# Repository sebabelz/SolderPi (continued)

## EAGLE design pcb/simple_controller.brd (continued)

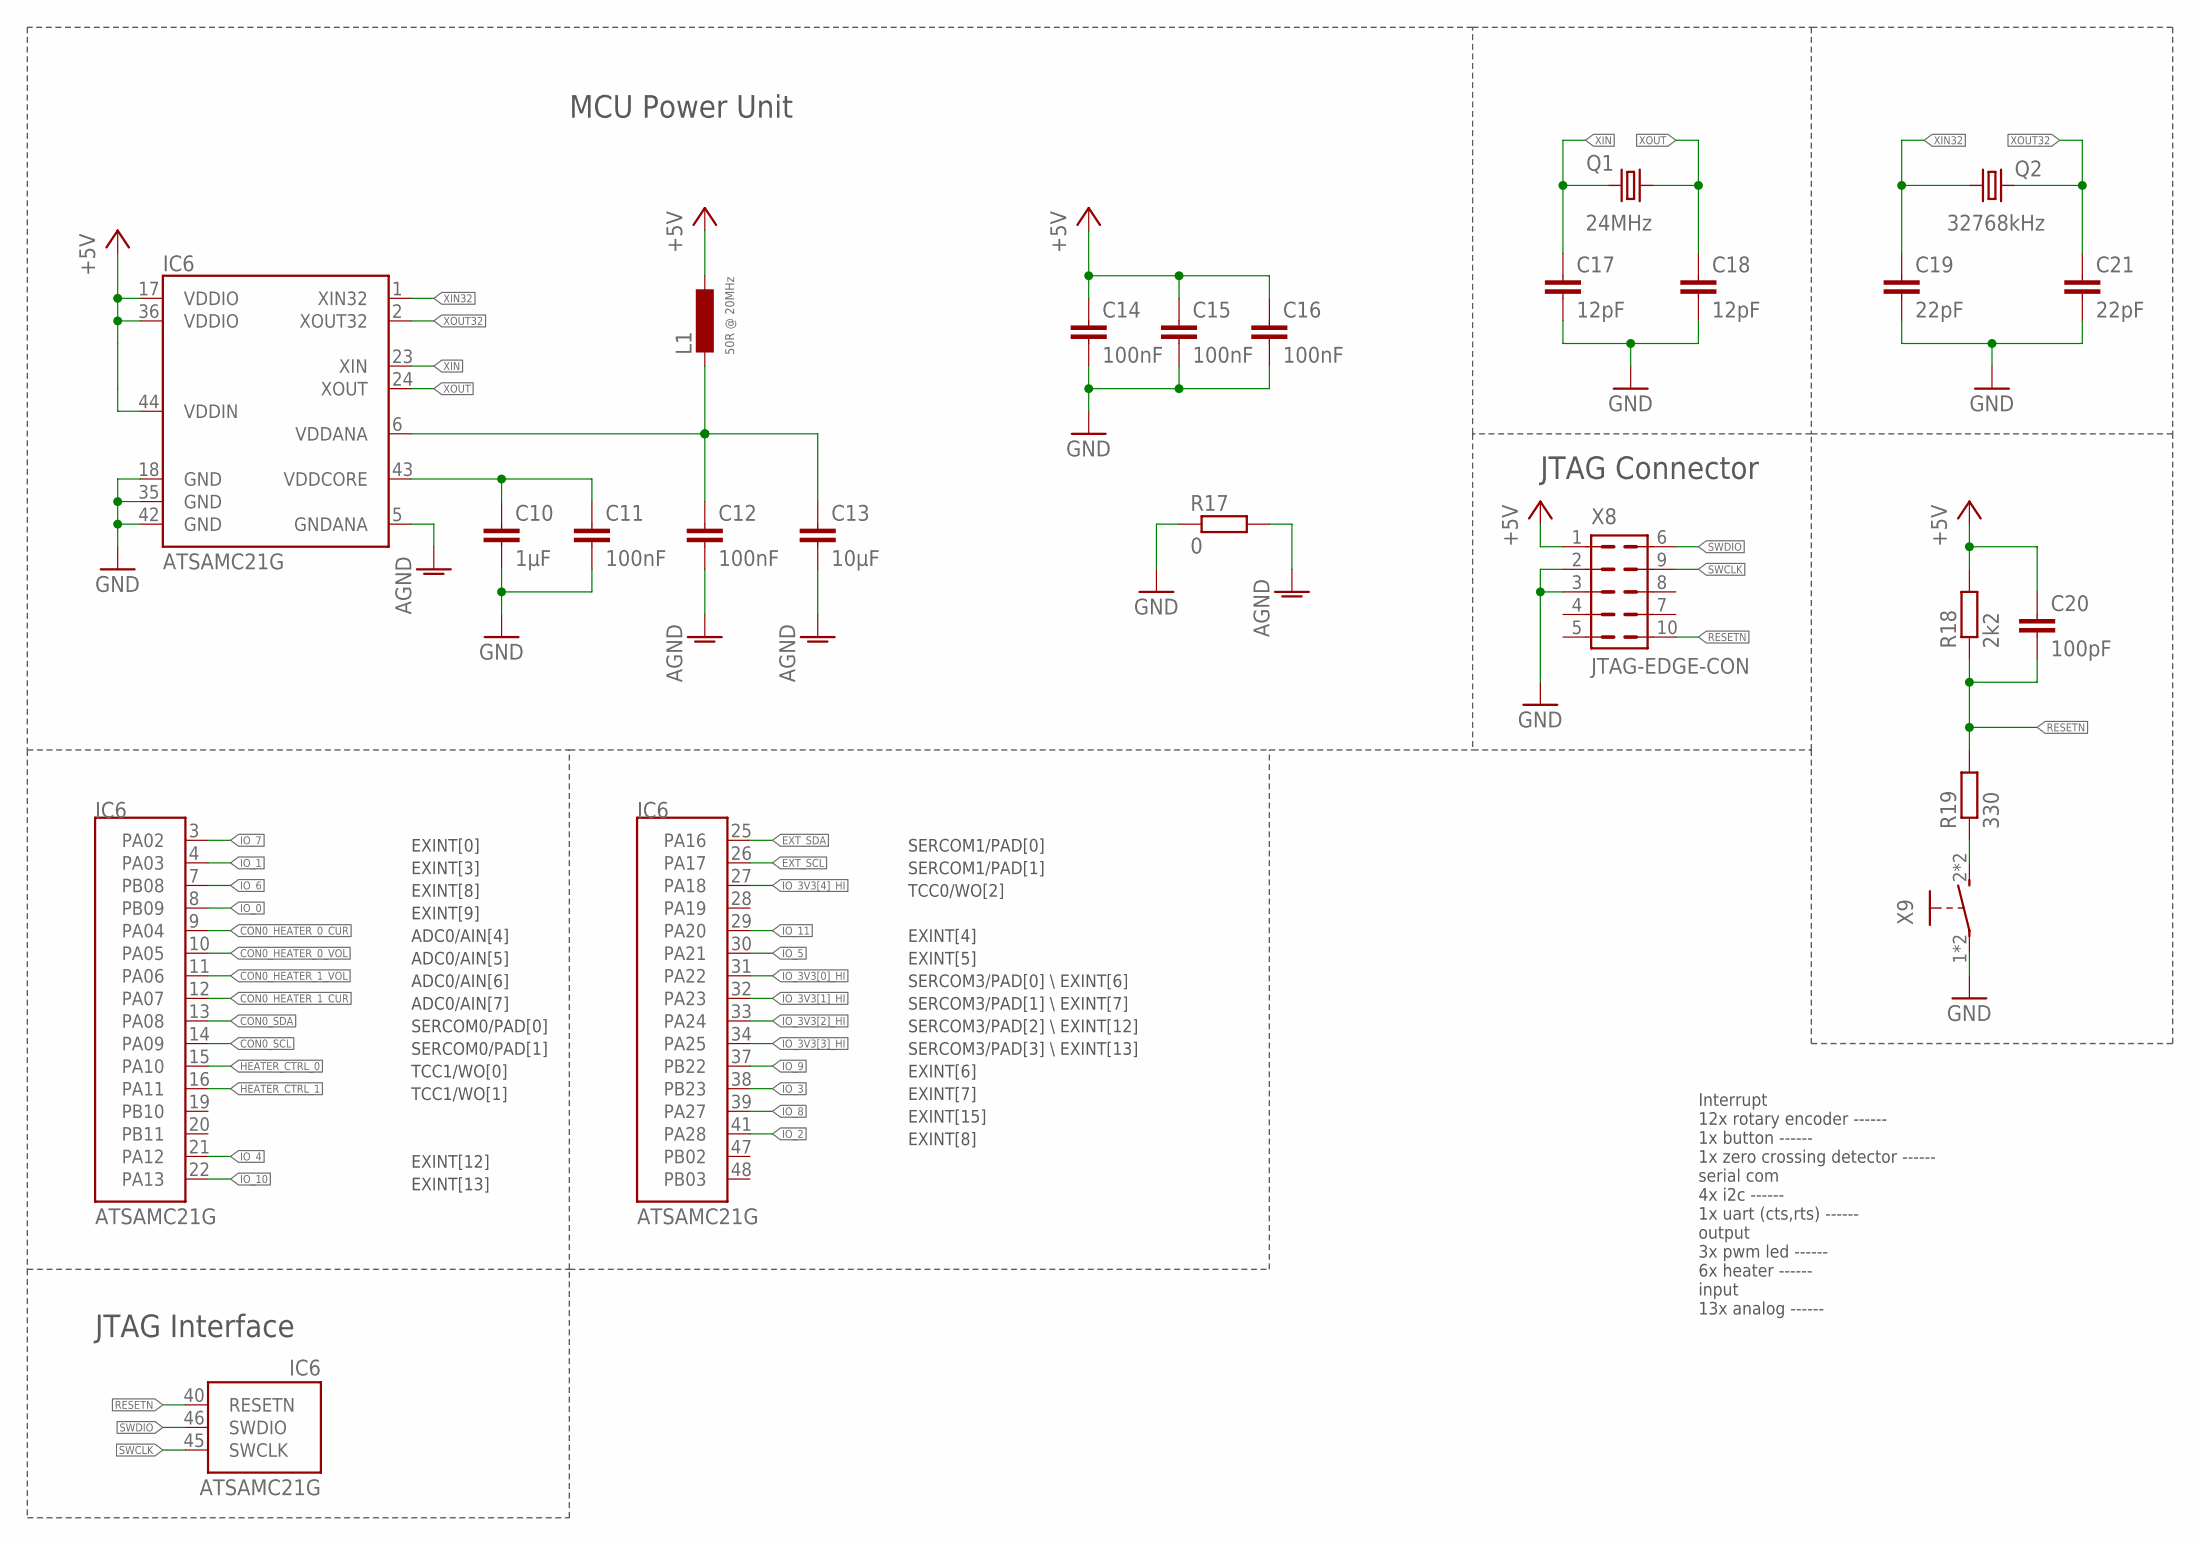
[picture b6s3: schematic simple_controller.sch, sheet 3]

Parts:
C10: 1µF; C0402
C11, C12, C14, C15, C16: 100nF; C0402
C13: 10µF; C0805
C17, C18: 12pF; C0402
C19, C21: 22pF; C0402
C20: 100pF; C0603
IC6: ATSAMC21G; TQFP48
L1: 50R @ 20MHz; L0603
Q1: 24MHz; HCR2520
Q2: 32768kHz; 2X1.2
R17: 0; R1210
R18: 2k2; R0603
R19: 330; R0603
X8: JTAG-EDGE-CON; DEBUG-CON
X9: B3S-1000; B3S

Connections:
+5V: C14.1, C15.1, C16.1, C20.1, IC6.17 (VDDIO), IC6.36 (VDDIO), IC6.44 (VDDIN), L1.1, R18.2, X8.1; also elsewhere on the board
AGND: C12.2, C13.2, IC6.5 (GNDANA), R17.2; also elsewhere on the board
CON0_HEATER_0_CUR: IC6.9 (PA04); also elsewhere on the board
CON0_HEATER_0_VOL: IC6.10 (PA05); also elsewhere on the board
CON0_HEATER_1_CUR: IC6.12 (PA07); also elsewhere on the board
CON0_HEATER_1_VOL: IC6.11 (PA06); also elsewhere on the board
CON0_SCL: IC6.14 (PA09); also elsewhere on the board
CON0_SDA: IC6.13 (PA08); also elsewhere on the board
EXT_SCL: IC6.26 (PA17); also elsewhere on the board
EXT_SDA: IC6.25 (PA16); also elsewhere on the board
GND: C10.2, C11.2, C14.2, C15.2, C16.2, C17.2, C18.2, C19.2, C21.2, IC6.18 (GND), IC6.35 (GND), IC6.42 (GND), R17.1, X8.2, X8.3, X9.1, X9.3; also elsewhere on the board
HEATER_CTRL_0: IC6.15 (PA10); also elsewhere on the board
HEATER_CTRL_1: IC6.16 (PA11); also elsewhere on the board
IO_0: IC6.8 (PB09); also elsewhere on the board
IO_1: IC6.4 (PA03); also elsewhere on the board
IO_2: IC6.41 (PA28); also elsewhere on the board
IO_3: IC6.38 (PB23); also elsewhere on the board
IO_3V3[0]_HI: IC6.31 (PA22); also elsewhere on the board
IO_3V3[1]_HI: IC6.32 (PA23); also elsewhere on the board
IO_3V3[2]_HI: IC6.33 (PA24); also elsewhere on the board
IO_3V3[3]_HI: IC6.34 (PA25); also elsewhere on the board
IO_3V3[4]_HI: IC6.27 (PA18); also elsewhere on the board
IO_4: IC6.21 (PA12); also elsewhere on the board
IO_5: IC6.30 (PA21); also elsewhere on the board
IO_6: IC6.7 (PB08); also elsewhere on the board
IO_7: IC6.3 (PA02); also elsewhere on the board
IO_8: IC6.39 (PA27); also elsewhere on the board
IO_9: IC6.37 (PB22); also elsewhere on the board
IO_10: IC6.22 (PA13); also elsewhere on the board
IO_11: IC6.29 (PA20); also elsewhere on the board
RESETN: C20.2, IC6.40 (RESETN), R18.1, R19.2, X8.10; also elsewhere on the board
RESET_SW_IN: R19.1, X9.2 (S), X9.4 (S)
SWCLK: IC6.45 (SWCLK), X8.9; also elsewhere on the board
SWDIO: IC6.46 (SWDIO), X8.6; also elsewhere on the board
VDDANA: C12.1, C13.1, IC6.6 (VDDANA), L1.2
VDDCORE: C10.1, C11.1, IC6.43 (VDDCORE)
XIN: C17.1, IC6.23 (XIN), Q1.1
XIN32: C19.1, IC6.1 (XIN32), Q2.1
XOUT: C18.1, IC6.24 (XOUT), Q1.2
XOUT32: C21.1, IC6.2 (XOUT32), Q2.2

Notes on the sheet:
Interrupt 12x rotary encoder ------ 1x button ------ 1x zero crossing detector ------ serial com 4x i2c ------ 1x uart (cts,rts) ------ output 3x pwm led ------ 6x heater ------ input 13x analog ------
JTAG Interface
JTAG Connector
MCU Power Unit
TCC1/WO[1]
TCC1/WO[0]
ADC0/AIN[4]
ADC0/AIN[5]
ADC0/AIN[6]
ADC0/AIN[7]
SERCOM0/PAD[0]
SERCOM0/PAD[1]
SERCOM1/PAD[0]
SERCOM1/PAD[1]
SERCOM3/PAD[0] \\ EXINT[6]
SERCOM3/PAD[1] \\ EXINT[7]
SERCOM3/PAD[2] \\ EXINT[12]
SERCOM3/PAD[3] \\ EXINT[13]
TCC0/WO[2]
EXINT[9]
EXINT[8]
EXINT[3]
EXINT[0]
EXINT[15]
EXINT[7]
EXINT[6]
EXINT[13]
EXINT[12]
EXINT[4]
EXINT[5]

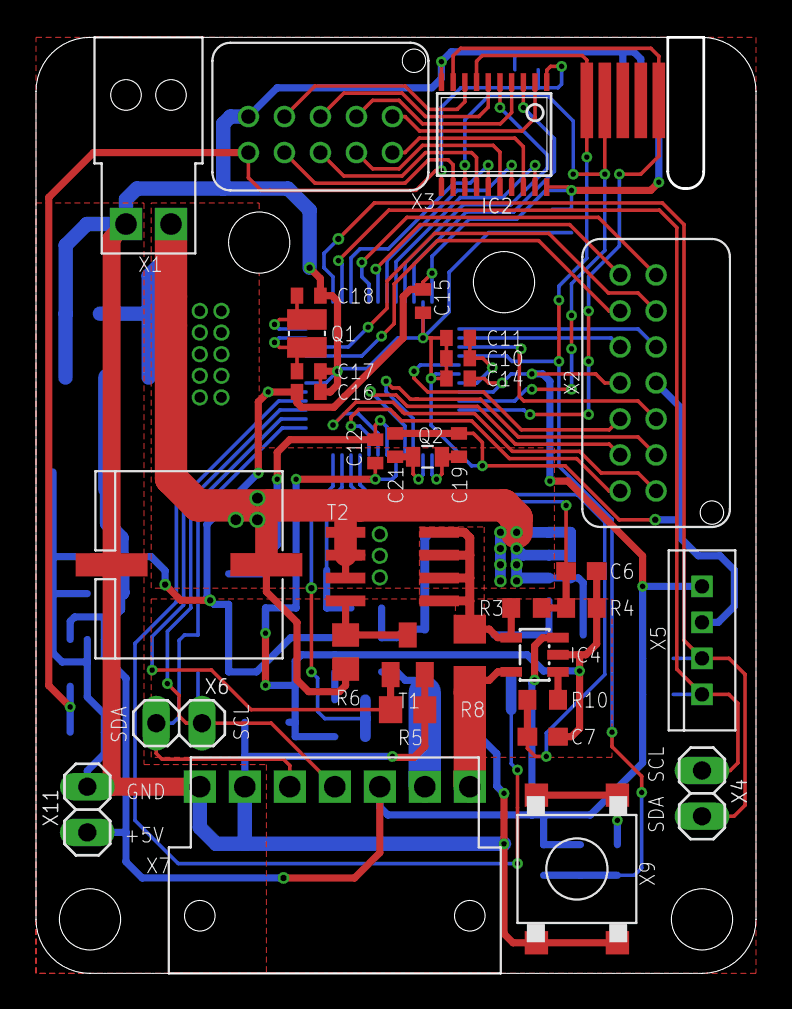
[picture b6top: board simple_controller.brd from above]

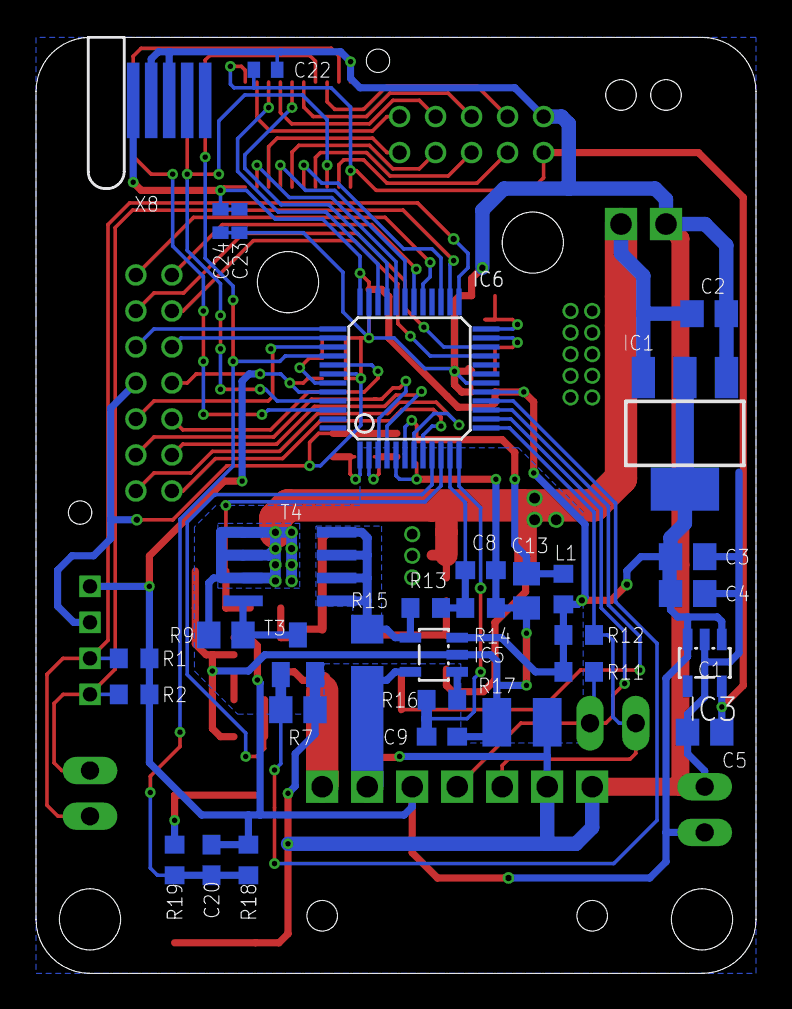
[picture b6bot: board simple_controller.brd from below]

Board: 2 copper layers, 39.8 x 51.9 mm, 66 parts (32 on the bottom side), 58 nets.

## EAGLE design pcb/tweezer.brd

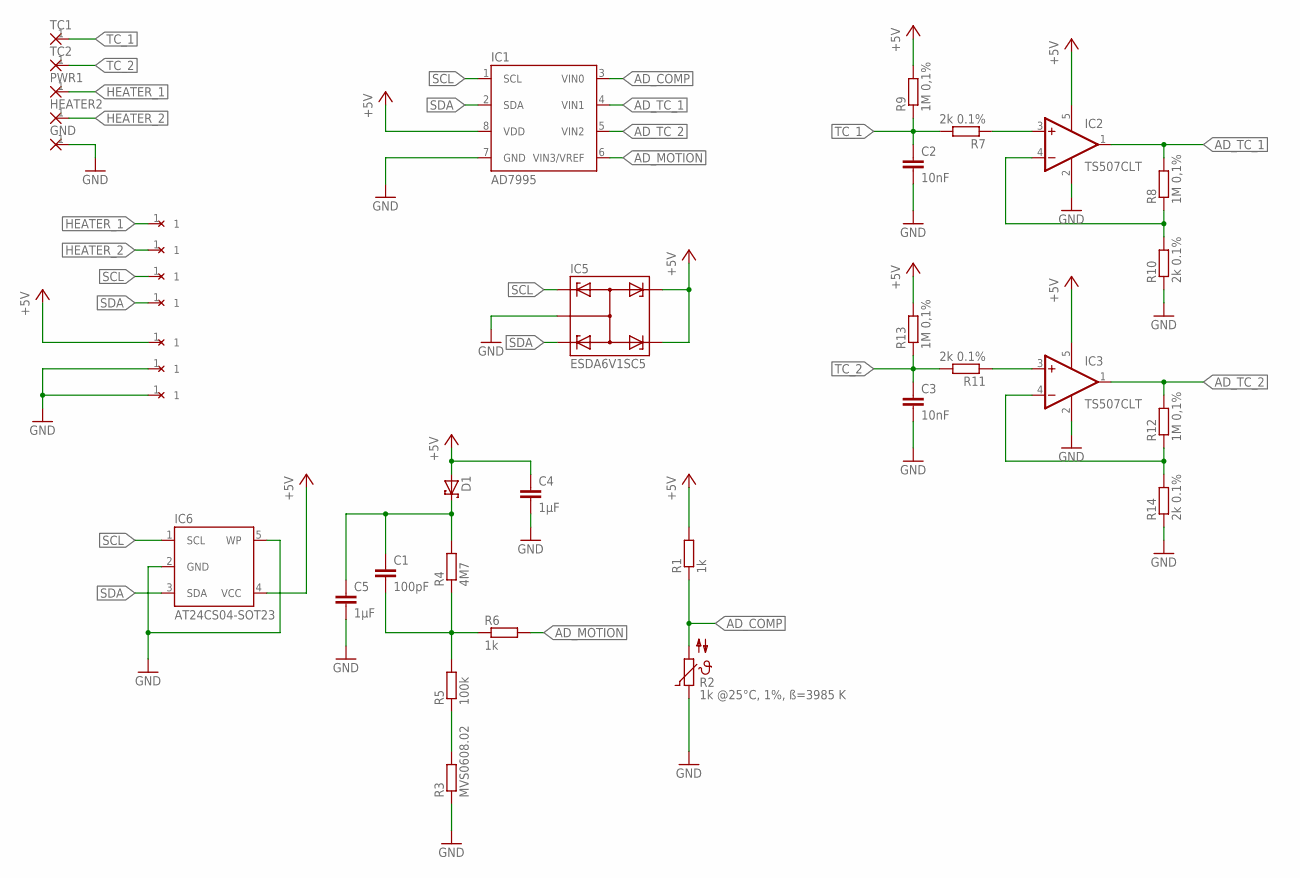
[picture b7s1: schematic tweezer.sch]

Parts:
21: WIREPAD
C1: 100pF; C0603
C2, C3: 10nF; C0603
C4, C5: 1µF; C0603
D1: BAT54H; SOD123-F
GND: 1,6/0,8
HEATER2: 1,6/0,8
IC1: AD7995; SOT23-8
IC2, IC3: TS507CLT; SOT23-5L
IC5: ESDA6V1SC5; SOT23-5L
IC6: AT24CS04-SOT23; SOT23-5L
PWR1: 1,6/0,8
R1, R6: 1k; R0603
R2: 1k @25°C, 1%, ß=3985 K; R0603
R3: MVS0608.02; VIBRA-SNS
R4: 4M7; R0603
R5: 100k; R0603
R7, R10, R11, R14: 2k 0.1%; R0603
R8, R9, R12, R13: 1M 0,1%; R0603
TC1, TC2: 1,6/0,8
U$1, U$7, U$9, U$10, U$11: WIREPAD
ß: WIREPAD

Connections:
+5V: C4.1, D1.2 (A), IC1.8 (VDD), IC2.5 (V+), IC3.5 (V+), IC5.4, IC5.5, IC6.4 (VCC), R1.2, R9.2, R13.2, U$10.1
AD_COMP: IC1.3 (VIN0), R1.1, R2.2
AD_MOTION: IC1.6 (VIN3/VREF), R6.2
AD_TC_1: IC1.4 (VIN1), IC2.1 (OUT), R8.2
AD_TC_2: IC1.5 (VIN2), IC3.1 (OUT), R12.2
FEEDBACK1: IC3.4 (-IN), R12.1, R14.2
FEEDBACK_TC_1: IC2.4 (-IN), R8.1, R10.2
GND: C2.2, C3.2, C4.2, C5.2, GND.1, IC1.7 (GND), IC2.2 (V-), IC3.2 (V-), IC5.2, IC6.2 (GND), IC6.5 (WP), R2.1, R3.P$1 (1), R10.1, R14.1, U$1.1, U$11.1
HEATER_1: PWR1.1, ß.1
HEATER_2: HEATER2.1, U$7.1
MOTION_DIV: R3.P$2 (2), R5.1
MOTION_FIL: C1.2, R4.1, R5.2, R6.1
unnamed: C1.1, C5.1, D1.1 (C), R4.2
SCL: 21.1, IC1.1 (SCL), IC5.1, IC6.1 (SCL)
SDA: IC1.2 (SDA), IC5.3, IC6.3 (SDA), U$9.1
TC_1: C2.1, R7.2, R9.1, TC1.1
TC_2: C3.1, R11.2, R13.1, TC2.1
THERMO_FIL1: IC3.3 (+IN), R11.1
THERMO_FIL_TC_1: IC2.3 (+IN), R7.1

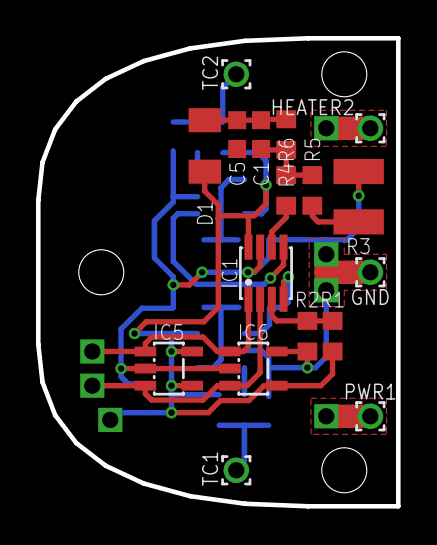
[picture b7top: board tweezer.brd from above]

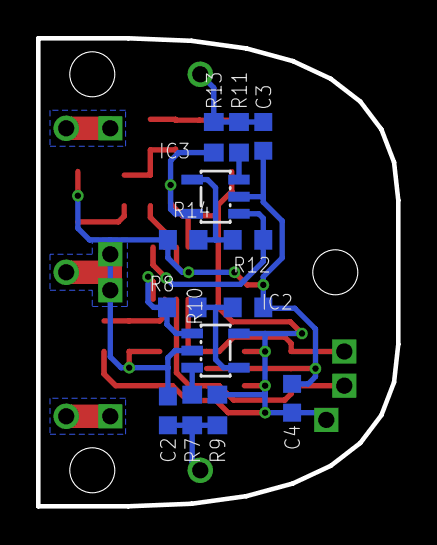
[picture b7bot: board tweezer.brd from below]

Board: 2 copper layers, 20.0 x 26.0 mm, 37 parts (13 on the bottom side), 19 nets.

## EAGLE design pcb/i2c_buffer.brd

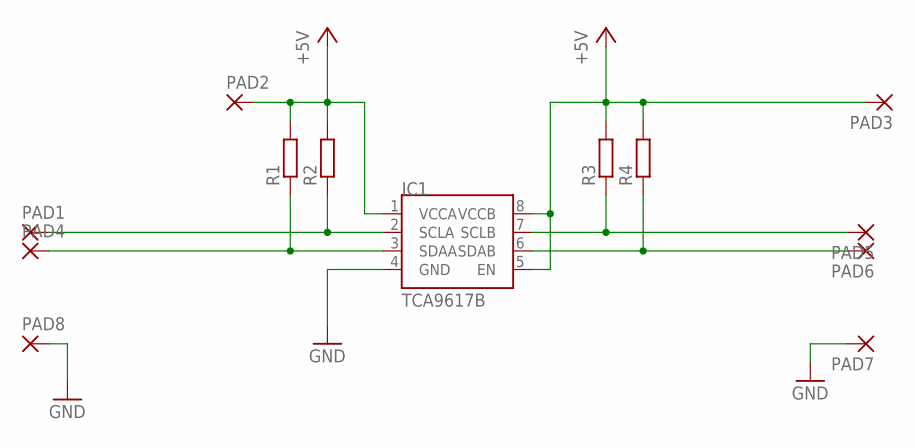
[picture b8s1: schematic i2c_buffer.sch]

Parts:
IC1: TCA9617B; VSSOP-8
PAD1, PAD2, PAD3, PAD4, PAD5, PAD6, PAD7, PAD8: 2,15/1,0
R1, R2, R3, R4: R-EU_R0805; R0805

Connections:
+5V: IC1.1 (VCCA), IC1.5 (EN), IC1.8 (VCCB), PAD2.1, PAD3.1, R1.2, R2.2, R3.2, R4.2
GND: IC1.4 (GND), PAD7.1, PAD8.1
unnamed: IC1.2 (SCLA), PAD1.1, R2.1
unnamed: IC1.3 (SDAA), PAD4.1, R1.1
unnamed: IC1.7 (SCLB), PAD5.1, R3.1
unnamed: IC1.6 (SDAB), PAD6.1, R4.1

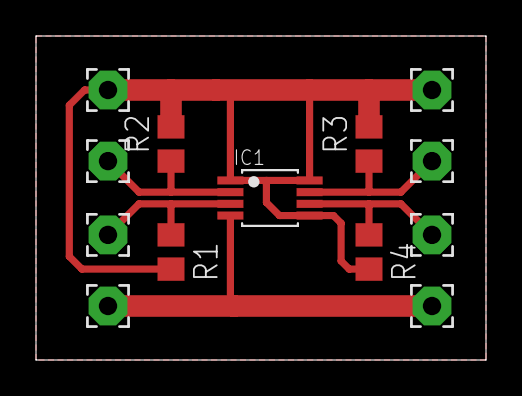
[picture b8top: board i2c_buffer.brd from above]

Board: 2 copper layers, 25.0 x 18.0 mm, 13 parts (0 on the bottom side), 6 nets.

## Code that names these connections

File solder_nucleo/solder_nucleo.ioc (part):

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Mcu.Name=STM32F446R(C-E)Tx
Mcu.Package=LQFP64
Mcu.UserName=STM32F446RETx
PA0-WKUP.GPIOParameters=GPIO_Speed
PA0-WKUP.GPIO_Speed=GPIO_SPEED_FREQ_HIGH
PA0-WKUP.Signal=S_TIM5_CH1
PA1.GPIOParameters=GPIO_Speed
PA1.GPIO_Speed=GPIO_SPEED_FREQ_HIGH
PA1.Signal=S_TIM5_CH2
PA10.GPIOParameters=GPIO_Label,GPIO_ModeDefaultEXTI
PA10.GPIO_Label=ENC_CH_A
PA10.GPIO_ModeDefaultEXTI=GPIO_MODE_IT_FALLING
PA10.Signal=GPXTI10
PA13.GPIOParameters=GPIO_Label
PA13.GPIO_Label=TMS
PA13.Mode=Serial_Wire
PA13.Signal=SYS_JTMS-SWDIO
PA14.GPIOParameters=GPIO_Label
PA14.GPIO_Label=TCK
PA14.Mode=Serial_Wire
PA14.Signal=SYS_JTCK-SWCLK
PA2.GPIOParameters=GPIO_Label
PA2.GPIO_Label=USART_TX
PA2.Mode=Asynchronous
PA2.Signal=USART2_TX
PA3.GPIOParameters=GPIO_Label
PA3.GPIO_Label=USART_RX
PA3.Mode=Asynchronous
PA3.Signal=USART2_RX
PA4.GPIOParameters=GPIO_Label
PA4.GPIO_Label=CMP
PA4.Signal=GPIO_Output
PA5.GPIOParameters=GPIO_Label
PA5.GPIO_Label=LD2 [Green Led]
PA5.Signal=GPIO_Output
PA6.Signal=S_TIM3_CH1
PA7.Signal=S_TIM3_CH2
PB3.GPIOParameters=GPIO_Label
PB3.GPIO_Label=SWO
PB3.Signal=SYS_JTDO-SWO
PB4.GPIOParameters=GPIO_Label
PB4.GPIO_Label=ENC_CH_B
PB4.Signal=GPIO_Input
PB5.GPIOParameters=GPIO_Label
PB5.GPIO_Label=BTN
PB5.Signal=GPXTI5
PB8.GPIOParameters=GPIO_PuPdOD
PB8.GPIO_PuPdOD=GPIO_PULLUP
PB8.Mode=I2C
PB8.Signal=I2C1_SCL
PB9.GPIOParameters=GPIO_PuPdOD
PB9.GPIO_PuPdOD=GPIO_PULLUP
PB9.Mode=I2C
PB9.Signal=I2C1_SDA
PC13.GPIOParameters=GPIO_Label,GPIO_ModeDefaultEXTI
PC13.GPIO_Label=B1 [Blue PushButton]
PC13.GPIO_ModeDefaultEXTI=GPIO_MODE_IT_FALLING
PC13.Signal=GPXTI13
PC14-OSC32_IN.Mode=LSE-External-Oscillator
PC14-OSC32_IN.Signal=RCC_OSC32_IN
PC15-OSC32_OUT.Mode=LSE-External-Oscillator
PC15-OSC32_OUT.Signal=RCC_OSC32_OUT
PC6.GPIOParameters=GPIO_PuPdOD
PC6.GPIO_PuPdOD=GPIO_NOPULL
PC6.Mode=I2C
PC6.Signal=FMPI2C1_SCL
PC7.GPIOParameters=GPIO_PuPdOD
PC7.GPIO_PuPdOD=GPIO_NOPULL
PC7.Mode=I2C
PC7.Signal=FMPI2C1_SDA
PH0-OSC_IN.Mode=HSE-External-Oscillator
PH0-OSC_IN.Signal=RCC_OSC_IN
PH1-OSC_OUT.Mode=HSE-External-Oscillator
PH1-OSC_OUT.Signal=RCC_OSC_OUT
RCC.HSE_VALUE=8000000
RCC.SYSCLKFreq_VALUE=84000000
RCC.SYSCLKSource=RCC_SYSCLKSOURCE_PLLCLK
board=NUCLEO-F446RE
boardIOC=true

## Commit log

2018-05-06 pcbs added
2018-05-06 bom added
2018-05-06 changed bom
2018-05-08 reworked current path on boards and added new gerber files
2018-05-15 added simple encoder
2018-05-25 updated simple controller, simple encoder
2018-05-26 updated simple controller, simple encoder (3D Packages)
2018-05-28 fixed vcc,vdd on opAmp
2018-05-31 fixing op amp (iron,tweezer)
2018-09-27 console View added
2018-09-27 reworked Terminal connection
2018-09-28 settings updated automatically
2018-11-18 updated Schematic from lib
2019-01-26 iron drills deleted
2019-03-07 qt ui added
2019-03-11 parts reworked
2019-03-26 changed part number ad7995
2019-03-27 read adc after pwm on state
2019-03-29 added button interrupt
2019-03-29 wip on capture software
2019-03-31 WIP: remove blocking TC function
2019-03-31 recording stops after heating up
2019-04-03 working
2019-04-14 arduino pid added
2019-04-18 pid settings changed
2019-07-27 basic configuration of nucleo board
2019-07-28 SSD1306 support added
2019-08-08 changed project to cpp
2019-08-08 working UART-Debugging connection
2019-08-08 debugging fmi2c
2019-08-09 reworked AD7995
2019-08-11 reworked PID
2019-08-11 working control parameters
2019-08-15 updated iron
2019-08-15 changed encoder to interrupt mode
2019-08-15 reworked iron parts
2019-08-18 reworked SolderingIron class
2019-08-21 i2c_buffer pcb added
2019-08-21 initial Commit controller Board
2019-08-23 wip connect mcu
2019-08-23 solderingIron class refactored
2019-08-23 circuit fully connected
2019-08-26 shottky diode added to iron/tweezer
2019-08-28 iron tweezer updated
2019-09-17 boms reworked
2021-08-15 kicad version pcb
2021-08-16 refactored debug connector
